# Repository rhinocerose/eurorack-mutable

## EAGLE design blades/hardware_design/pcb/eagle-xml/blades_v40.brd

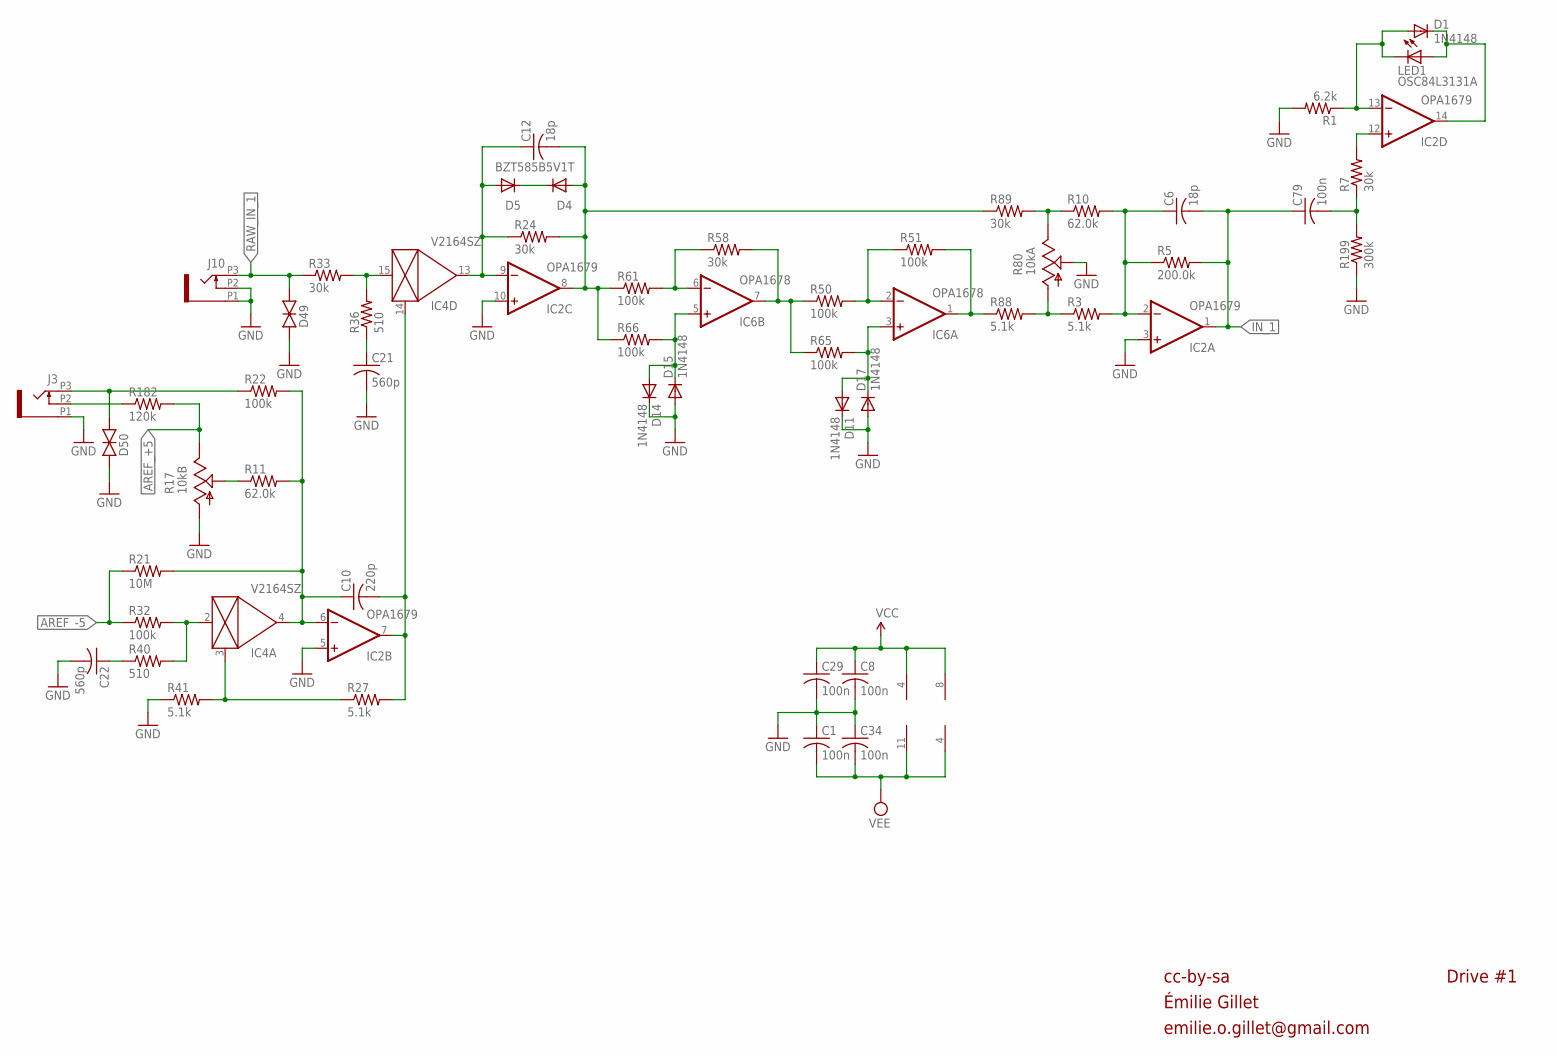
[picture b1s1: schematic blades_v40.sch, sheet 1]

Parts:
C1, C8, C29, C34, C79: 100n; C0402
C6, C12: 18p; C0402
C10: 220p; C0402
C21, C22: 560p; C0402
D1, D11, D14, D15, D17: 1N4148; SOD523
D4, D5: BZT585B5V1T; SOD523
D49, D50: TVS; 0603
IC2: OPA1679; TSSOP14_065
IC4: V2164SZ; SOIC16N
IC6: OPA1678; VSSOP8
J3, J10: PJ301_THONKICONNTME; WQP_PJ_301M_TME
LED1: OSC84L3131A; LED3MM
R1: 6.2k; R0402
R3, R27, R41, R88: 5.1k; R0402
R5: 200.0k; R0402
R7, R24, R33, R58, R89: 30k; R0402
R10, R11: 62.0k; R0402
R17: 10kB; ALPS_POT_VERTICAL_PS
R21: 10M; R0402
R22, R32, R50, R51, R61, R65, R66: 100k; R0402
R36, R40: 510; R0402
R80: 10kA; ALPS_POT_NARROW
R182: 120k; R0402
R199: 300k; R0402

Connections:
AREF_+5: R17.P$1 (E), R182.2; also elsewhere on the board
AREF_-5: R21.1, R32.1; also elsewhere on the board
DRIVE_1: C12.2, D4.A, IC2.8 (OUT), R24.2, R61.1, R66.1, R89.1
GND: C1.1, C8.2, C21.2, C22.2, C29.2, C34.1, D11.C, D14.C, D15.A, D17.A, D49.1 (A), D50.1 (A), IC2.3 (+IN), IC2.5 (+IN), IC2.10 (+IN), J3.P1 (1), J10.P1 (1), J10.P2 (2), R1.2, R17.P$3 (A), R41.1, R80.P$2 (S), R199.1; also elsewhere on the board
IN_1: C6.2, C79.1, IC2.1 (OUT), R5.2; also elsewhere on the board
MORPH_1A1: C10.2, IC2.7 (OUT), IC4.14 (CTRL), R27.2
unnamed: D4.C, D5.C
unnamed: C21.1, R36.1
unnamed: C79.2, R7.1, R199.2
unnamed: IC4.2 (IN), R32.2, R40.2
unnamed: IC2.12 (+IN), R7.2
unnamed: R10.1, R80.P$1 (E), R89.2
unnamed: IC6.6 (-IN), R58.1, R61.2
unnamed: D50.2 (C), J3.P3 (3), R22.1
unnamed: C10.1, IC2.6 (-IN), IC4.4 (OUT), R11.2, R21.2, R22.2
unnamed: R3.1, R80.P$3 (A), R88.2
unnamed: C6.1, IC2.2 (-IN), R3.2, R5.1, R10.2
unnamed: R11.1, R17.P$2 (S)
unnamed: IC4.3 (CTRL), R27.1, R41.2
unnamed: J3.P2 (2), R182.1
unnamed: C22.1, R40.1
unnamed: IC4.15 (IN), R33.2, R36.2
unnamed: D1.A, IC2.13 (-IN), LED1.K (C), R1.1
unnamed: C12.1, D5.A, IC2.9 (-IN), IC4.13 (OUT), R24.1
unnamed: D14.A, D15.C, IC6.5 (+IN), R66.2
unnamed: D1.C, IC2.14 (OUT), LED1.A
unnamed: IC6.7 (OUT), R50.1, R58.2, R65.1
unnamed: IC6.2 (-IN), R50.2, R51.1
unnamed: IC6.1 (OUT), R51.2, R88.1
unnamed: D11.A, D17.C, IC6.3 (+IN), R65.2
RAW_IN_1: D49.2 (C), J10.P3 (3), R33.1; also elsewhere on the board
VCC: C8.1, C29.1, IC2.4 (V+), IC6.8 (V+); also elsewhere on the board
VEE: C1.2, C34.2, IC2.11 (V-), IC6.4 (V-); also elsewhere on the board

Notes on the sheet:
cc-by-sa
Émilie Gillet
emilie.o.gillet@gmail.com
Drive #1

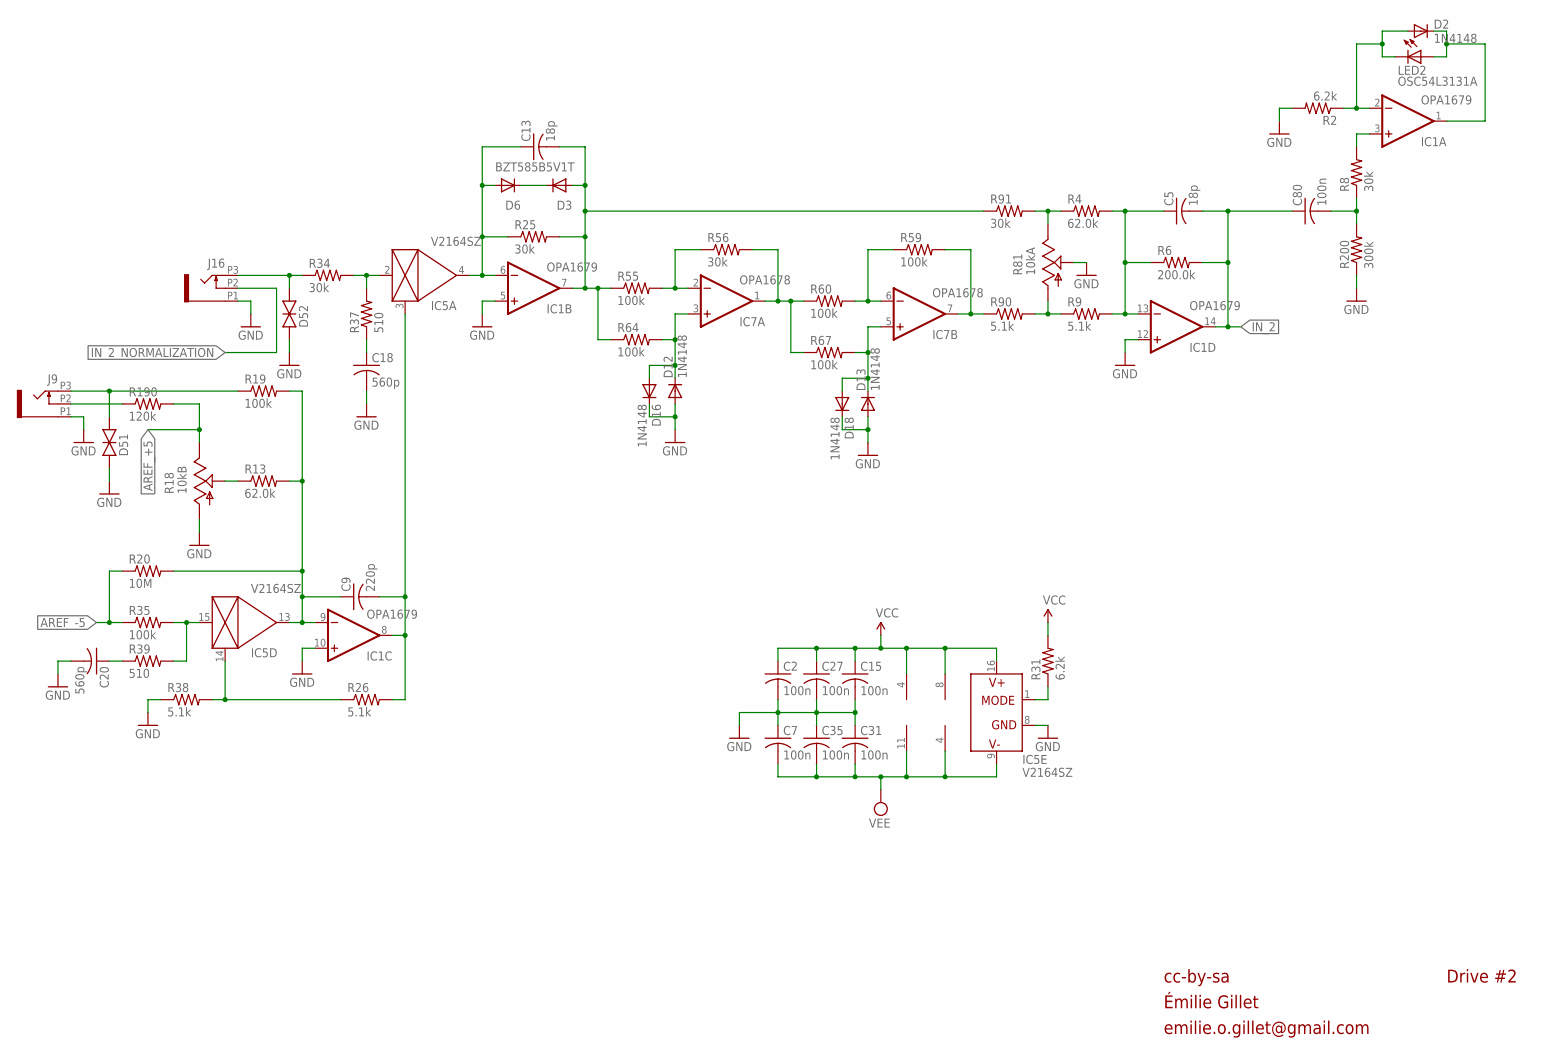
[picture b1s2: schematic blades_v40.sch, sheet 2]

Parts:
C2, C7, C15, C27, C31, C35, C80: 100n; C0402
C5, C13: 18p; C0402
C9: 220p; C0402
C18, C20: 560p; C0402
D2, D12, D13, D16, D18: 1N4148; SOD523
D3, D6: BZT585B5V1T; SOD523
D51, D52: TVS; 0603
IC1: OPA1679; TSSOP14_065
IC5: V2164SZ; SOIC16N
IC7: OPA1678; VSSOP8
J9, J16: PJ301_THONKICONNTME; WQP_PJ_301M_TME
LED2: OSC54L3131A; LED3MM
R2, R31: 6.2k; R0402
R4, R13: 62.0k; R0402
R6: 200.0k; R0402
R8, R25, R34, R56, R91: 30k; R0402
R9, R26, R38, R90: 5.1k; R0402
R18: 10kB; ALPS_POT_VERTICAL_PS
R19, R35, R55, R59, R60, R64, R67: 100k; R0402
R20: 10M; R0402
R37, R39: 510; R0402
R81: 10kA; ALPS_POT_NARROW
R190: 120k; R0402
R200: 300k; R0402

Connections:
AREF_+5: R18.P$1 (E), R190.2; also elsewhere on the board
AREF_-5: R20.1, R35.1; also elsewhere on the board
DRIVE_2: C13.2, D3.A, IC1.7 (OUT), R25.2, R55.1, R64.1, R91.1
GND: C2.2, C7.1, C15.2, C18.2, C20.2, C27.2, C31.1, C35.1, D12.A, D13.A, D16.C, D18.C, D51.1 (A), D52.1 (A), IC1.5 (+IN), IC1.10 (+IN), IC1.12 (+IN), IC5.8 (GND), J9.P1 (1), J16.P1 (1), R2.2, R18.P$3 (A), R38.1, R81.P$2 (S), R200.1; also elsewhere on the board
IN_1LED1: IC1.3 (+IN), R8.2
IN_2: C5.2, C80.1, IC1.14 (OUT), R6.2; also elsewhere on the board
IN_2_NORMALIZATION: J16.P2 (2); also elsewhere on the board
MORPH_1A2: C9.2, IC1.8 (OUT), IC5.3 (CTRL), R26.2
unnamed: D2.A, IC1.2 (-IN), LED2.K (C), R2.1
unnamed: R13.1, R18.P$2 (S)
unnamed: IC7.2 (-IN), R55.2, R56.1
unnamed: D12.C, D16.A, IC7.3 (+IN), R64.2
unnamed: IC7.1 (OUT), R56.2, R60.1, R67.1
unnamed: IC7.6 (-IN), R59.1, R60.2
unnamed: J9.P2 (2), R190.1
unnamed: IC7.7 (OUT), R59.2, R90.1
unnamed: D51.2 (C), J9.P3 (3), R19.1
unnamed: C5.1, IC1.13 (-IN), R4.2, R6.1, R9.2
unnamed: IC5.1 (MODE), R31.1
unnamed: C80.2, R8.1, R200.2
unnamed: D2.C, IC1.1 (OUT), LED2.A
unnamed: C9.1, IC1.9 (-IN), IC5.13 (OUT), R13.2, R19.2, R20.2
unnamed: IC5.14 (CTRL), R26.1, R38.2
unnamed: IC5.15 (IN), R35.2, R39.2
unnamed: C20.1, R39.1
unnamed: C18.1, R37.1
unnamed: IC5.2 (IN), R34.2, R37.2
unnamed: C13.1, D6.A, IC1.6 (-IN), IC5.4 (OUT), R25.1
unnamed: D13.C, D18.A, IC7.5 (+IN), R67.2
unnamed: R4.1, R81.P$1 (E), R91.2
unnamed: R9.1, R81.P$3 (A), R90.2
unnamed: D3.C, D6.C
RAW_IN_2: D52.2 (C), J16.P3 (3), R34.1
VCC: C2.1, C15.1, C27.1, IC1.4 (V+), IC5.16 (V+), IC7.8 (V+), R31.2; also elsewhere on the board
VEE: C7.2, C31.2, C35.2, IC1.11 (V-), IC5.9 (V-), IC7.4 (V-); also elsewhere on the board

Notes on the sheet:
Drive #2
cc-by-sa
Émilie Gillet
emilie.o.gillet@gmail.com

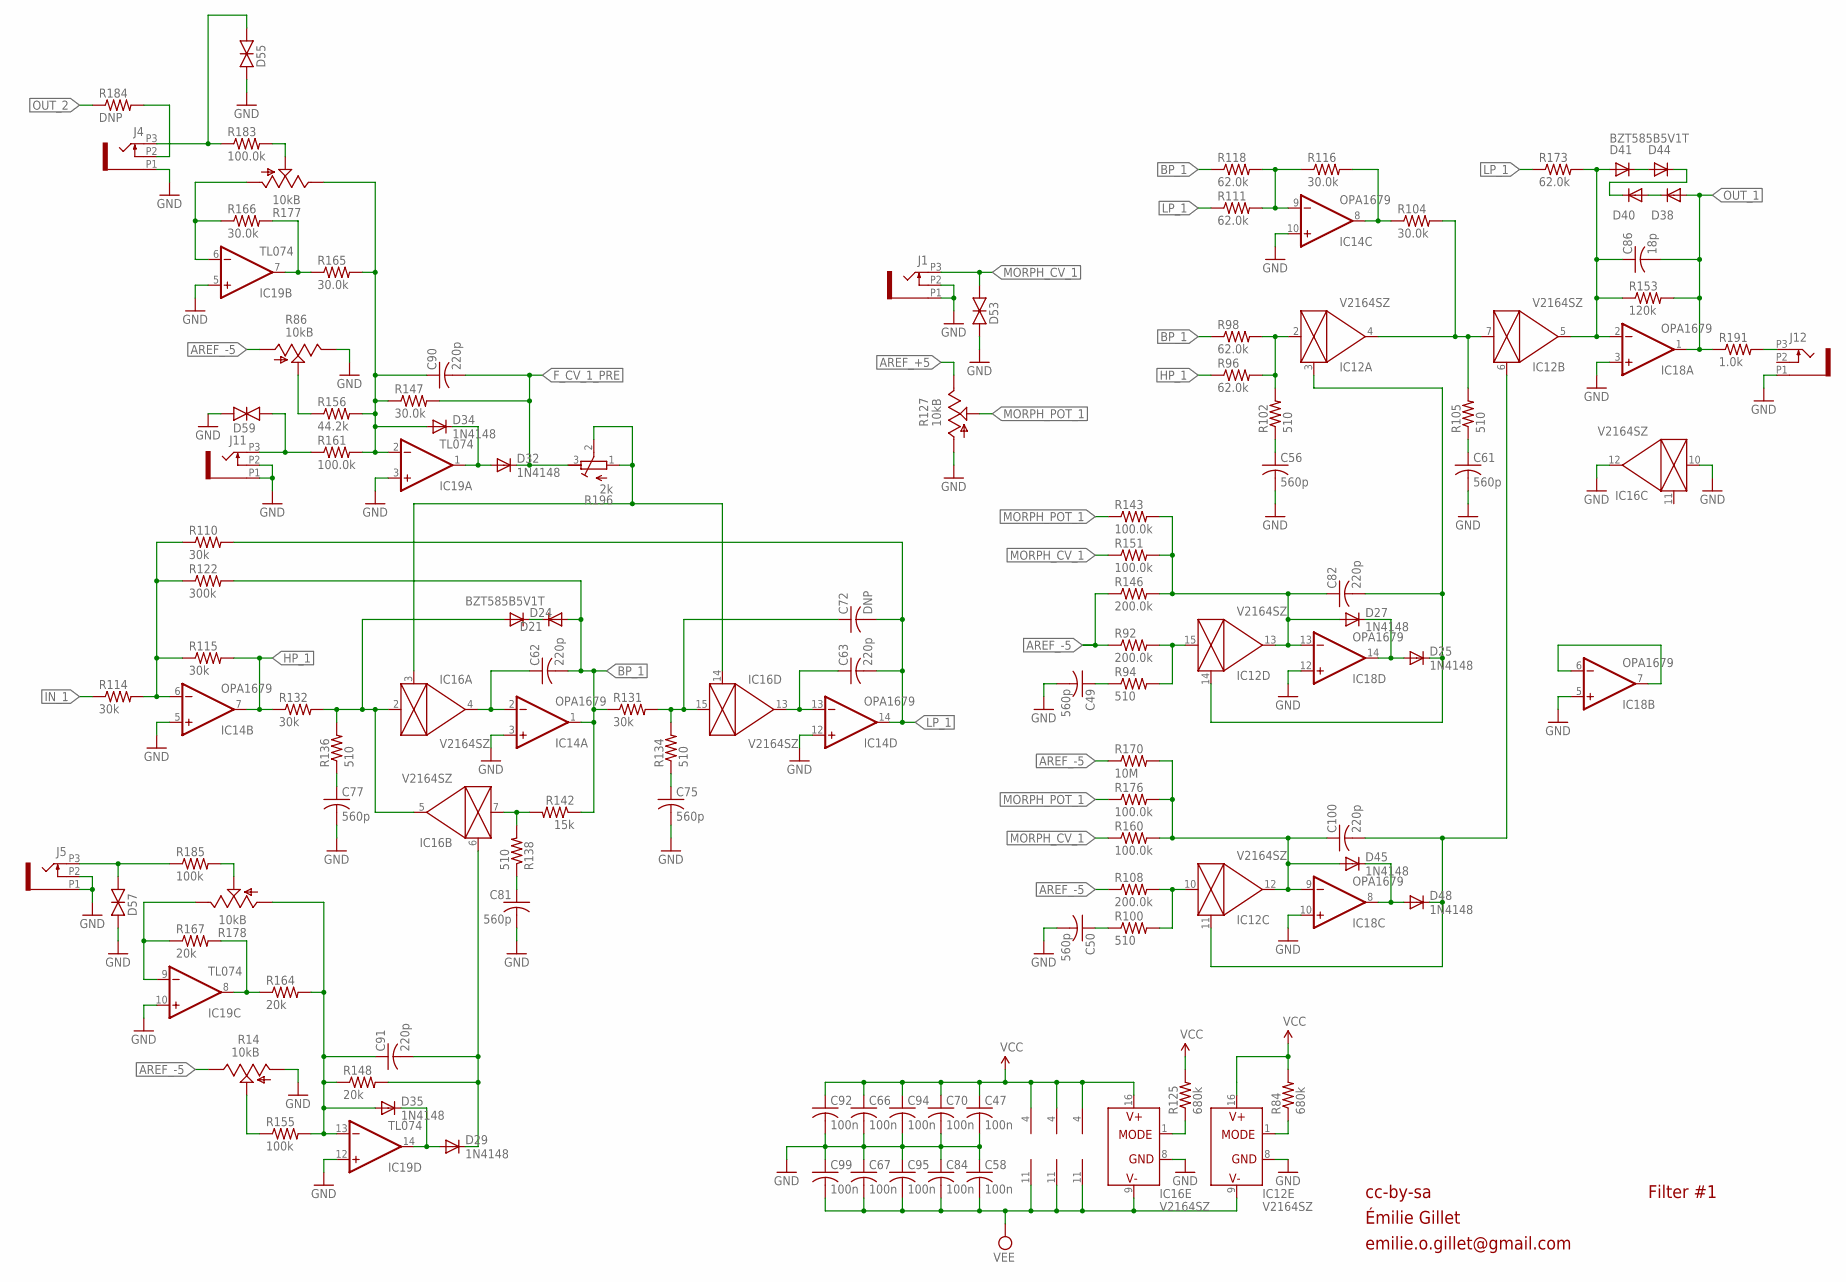
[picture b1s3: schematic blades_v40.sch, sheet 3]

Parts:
C47, C58, C66, C67, C70, C84, C92, C94, C95, C99: 100n; C0402
C49, C50, C56, C61, C75, C77, C81: 560p; C0402
C62, C63, C82, C90, C91, C100: 220p; C0402
C72: DNP; C0402
C86: 18p; C0402
D21, D24, D38, D40, D41, D44: BZT585B5V1T; SOD523
D25, D27, D29, D32, D34, D35, D45, D48: 1N4148; SOD523
D53, D55, D57, D59: TVS; 0603
IC12, IC16: V2164SZ; SOIC16N
IC14, IC18: OPA1679; TSSOP14_065
IC19: TL074; TSSOP14_065
J1, J4, J5, J11, J12: PJ301_THONKICONNTME; WQP_PJ_301M_TME
R14, R86, R127: 10kB; ALPS_POT_VERTICAL_PS
R84, R125: 680k; R0402
R92, R108, R146: 200.0k; R0402
R94, R100, R102, R105, R134, R136, R138: 510; R0402
R96, R98, R111, R118, R173: 62.0k; R0402
R104, R116, R147, R165, R166: 30.0k; R0402
R110, R114, R115, R131, R132: 30k; R0402
R122: 300k; R0402
R142: 15k; R0402
R143, R151, R160, R161, R176, R183: 100.0k; R0402
R148, R164, R167: 20k; R0402
R153: 120k; R0402
R155, R185: 100k; R0402
R156: 44.2k; R0402
R170: 10M; R0402
R177, R178: 10kB; ALPS_POT_NARROW
R184: DNP; R0603
R191: 1.0k; R0603
R196: 2k; RTRIM3296W

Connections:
AREF_+5: R127.P$1 (E); also elsewhere on the board
AREF_-5: R14.P$1 (E), R86.P$3 (A), R92.1, R108.1, R146.1, R170.1; also elsewhere on the board
BP_1: C62.2, D21.A, IC14.1 (OUT), R98.1, R118.1, R122.2, R131.1, R142.1
F_CV_1: IC16.3 (CTRL), IC16.14 (CTRL), R196.1 (E), R196.2 (S)
F_CV_1_PRE: C90.2, D32.C, R147.2, R196.3 (A); also elsewhere on the board
GND: C47.2, C49.2, C50.2, C56.2, C58.1, C61.2, C66.2, C67.1, C70.2, C75.2, C77.2, C81.2, C84.1, C92.2, C94.2, C95.1, C99.1, D53.1 (A), D55.1 (A), D57.1 (A), D59.1 (A), IC12.8 (GND), IC14.3 (+IN), IC14.5 (+IN), IC14.10 (+IN), IC14.12 (+IN), IC16.8 (GND), IC16.10 (IN), IC16.12 (OUT), IC18.3 (+IN), IC18.5 (+IN), IC18.10 (+IN), IC18.12 (+IN), IC19.3 (+IN), IC19.5 (+IN), IC19.10 (+IN), IC19.12 (+IN), J1.P1 (1), J1.P2 (2), J4.P1 (1), J5.P1 (1), J5.P2 (2), J11.P1 (1), J11.P2 (2), J12.P1 (1), R14.P$3 (A), R86.P$1 (E), R127.P$3 (A); also elsewhere on the board
HP_1: IC14.7 (OUT), R96.1, R115.2, R132.1
IN_1: R114.1; also elsewhere on the board
LP_1: C63.2, C72.2, IC14.14 (OUT), R110.2, R111.1, R173.1
MORPH_1A: C82.2, D25.C, IC12.3 (CTRL), IC12.14 (CTRL)
MORPH_1B: C100.2, D48.C, IC12.6 (CTRL), IC12.11 (CTRL)
MORPH_CV_1: D53.2 (C), J1.P3 (3), R151.1, R160.1
MORPH_POT_1: R127.P$2 (S), R143.1, R176.1
unnamed: C77.1, R136.1
unnamed: J12.P3 (3), R191.2
unnamed: C90.1, D34.A, IC19.2 (-IN), R147.1, R156.2, R161.2, R165.2, R177.P$1 (E)
unnamed: C91.1, D35.A, IC19.13 (-IN), R148.1, R155.2, R164.2, R178.P$3 (A)
unnamed: D32.A, D34.C, IC19.1 (OUT)
unnamed: R86.P$2 (S), R156.1
unnamed: IC19.9 (-IN), R167.1, R178.P$1 (E)
unnamed: IC19.8 (OUT), R164.1, R167.2
unnamed: R178.P$2 (S), R185.2
unnamed: C100.1, D45.A, IC12.12 (OUT), IC18.9 (-IN), R160.2, R170.2, R176.2
unnamed: IC14.6 (-IN), R110.1, R114.2, R115.1, R122.1
unnamed: C62.1, IC14.2 (-IN), IC16.4 (OUT)
unnamed: C75.1, R134.1
unnamed: C72.1, IC16.15 (IN), R131.2, R134.2
unnamed: C63.1, IC14.13 (-IN), IC16.13 (OUT)
unnamed: C81.1, R138.1
unnamed: IC16.7 (IN), R138.2, R142.2
unnamed: D57.2 (C), J5.P3 (3), R185.1
unnamed: D29.A, D35.C, IC19.14 (OUT)
unnamed: IC18.6 (-IN), IC18.7 (OUT)
unnamed: J4.P2 (2), R184.2
unnamed: R14.P$2 (S), R155.1
unnamed: IC12.2 (IN), R96.2, R98.2, R102.2
unnamed: IC14.9 (-IN), R111.2, R116.1, R118.2
unnamed: IC14.8 (OUT), R104.1, R116.2
unnamed: IC12.4 (OUT), IC12.7 (IN), R104.2, R105.2
unnamed: C56.1, R102.1
unnamed: C61.1, R105.1
unnamed: D45.C, D48.A, IC18.8 (OUT)
unnamed: IC12.10 (IN), R100.2, R108.2
unnamed: IC19.6 (-IN), R166.1, R177.P$3 (A)
unnamed: IC19.7 (OUT), R165.1, R166.2
unnamed: R177.P$2 (S), R183.2
unnamed: D55.2 (C), J4.P3 (3), R183.1
unnamed: D59.2 (C), J11.P3 (3), R161.1
unnamed: C50.1, R100.1
unnamed: IC12.15 (IN), R92.2, R94.2
unnamed: C49.1, R94.1
unnamed: C82.1, D27.A, IC12.13 (OUT), IC18.13 (-IN), R143.2, R146.2, R151.2
unnamed: D25.A, D27.C, IC18.14 (OUT)
unnamed: IC12.1 (MODE), R84.1
unnamed: IC16.1 (MODE), R125.1
unnamed: D21.C, D24.C
unnamed: C86.1, D41.A, IC12.5 (OUT), IC18.2 (-IN), R153.1, R173.2
unnamed: D38.C, D40.A
unnamed: D24.A, IC16.2 (IN), IC16.5 (OUT), R132.2, R136.2
unnamed: D40.C, D44.C
unnamed: D41.C, D44.A
OUT_1: C86.2, D38.A, IC18.1 (OUT), R153.2, R191.1; also elsewhere on the board
OUT_2: R184.1; also elsewhere on the board
RESONANCE_SUM_1: C91.2, D29.C, IC16.6 (CTRL), R148.2
VCC: C47.1, C66.1, C70.1, C92.1, C94.1, IC12.16 (V+), IC14.4 (V+), IC16.16 (V+), IC18.4 (V+), IC19.4 (V+), R84.2, R125.2; also elsewhere on the board
VEE: C58.2, C67.2, C84.2, C95.2, C99.2, IC12.9 (V-), IC14.11 (V-), IC16.9 (V-), IC18.11 (V-), IC19.11 (V-); also elsewhere on the board

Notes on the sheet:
Filter #1
cc-by-sa
Émilie Gillet
emilie.o.gillet@gmail.com

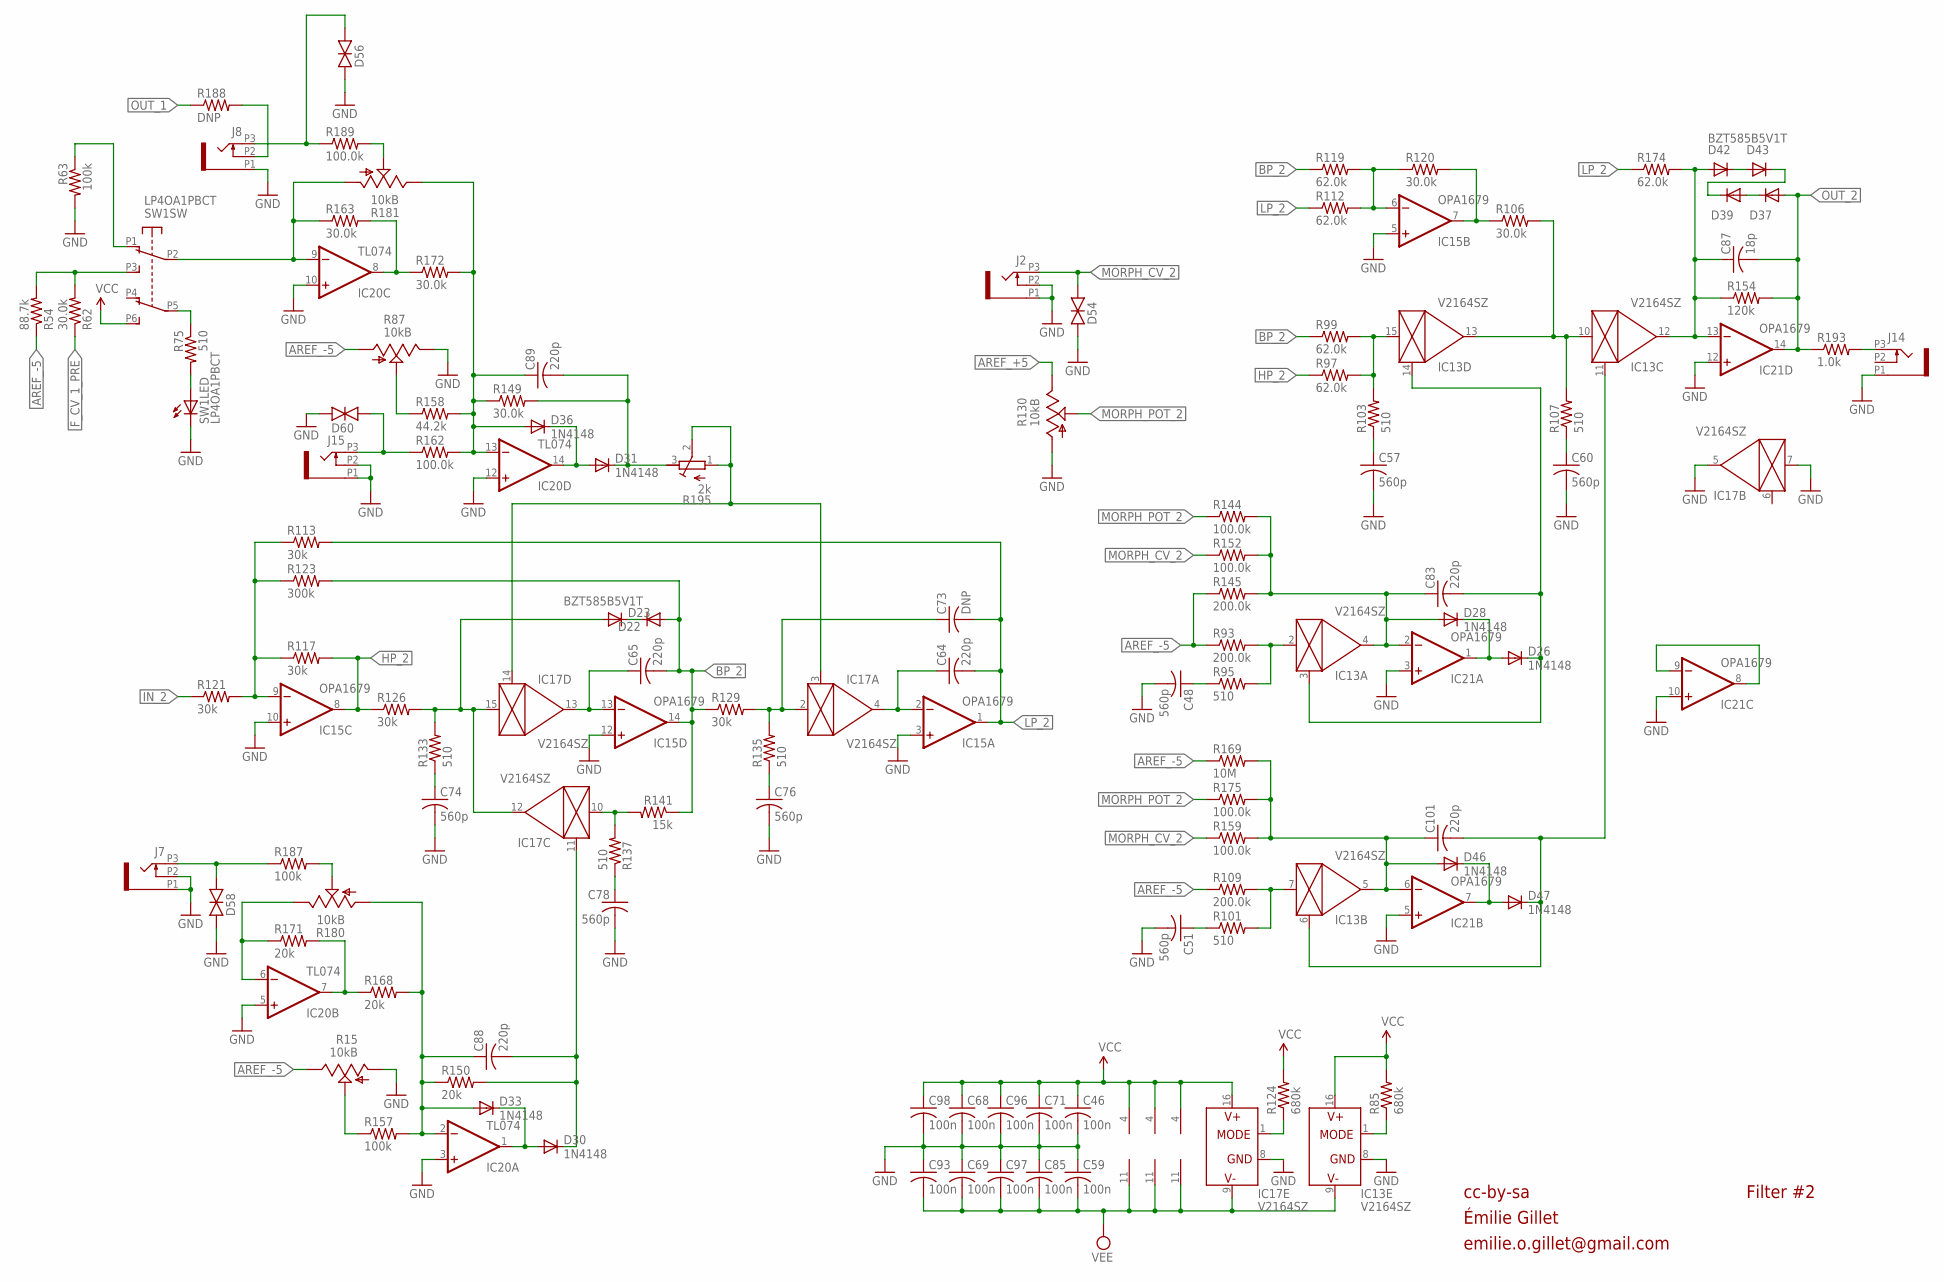
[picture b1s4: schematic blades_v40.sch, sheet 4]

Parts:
C46, C59, C68, C69, C71, C85, C93, C96, C97, C98: 100n; C0402
C48, C51, C57, C60, C74, C76, C78: 560p; C0402
C64, C65, C83, C88, C89, C101: 220p; C0402
C73: DNP; C0402
C87: 18p; C0402
D22, D23, D37, D39, D42, D43: BZT585B5V1T; SOD523
D26, D28, D30, D31, D33, D36, D46, D47: 1N4148; SOD523
D54, D56, D58, D60: TVS; 0603
IC13, IC17: V2164SZ; SOIC16N
IC15, IC21: OPA1679; TSSOP14_065
IC20: TL074; TSSOP14_065
J2, J7, J8, J14, J15: PJ301_THONKICONNTME; WQP_PJ_301M_TME
R15, R87, R130: 10kB; ALPS_POT_VERTICAL_PS
R54: 88.7k; R0402
R62, R106, R120, R149, R163, R172: 30.0k; R0402
R63, R157, R187: 100k; R0402
R75, R95, R101, R103, R107, R133, R135, R137: 510; R0402
R85, R124: 680k; R0402
R93, R109, R145: 200.0k; R0402
R97, R99, R112, R119, R174: 62.0k; R0402
R113, R117, R121, R126, R129: 30k; R0402
R123: 300k; R0402
R141: 15k; R0402
R144, R152, R159, R162, R175, R189: 100.0k; R0402
R150, R168, R171: 20k; R0402
R154: 120k; R0402
R158: 44.2k; R0402
R169: 10M; R0402
R180, R181: 10kB; ALPS_POT_NARROW
R188: DNP; R0603
R193: 1.0k; R0603
R195: 2k; RTRIM3296W
SW1: LP4OA1PBCT

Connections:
AREF_+5: R130.P$1 (E); also elsewhere on the board
AREF_-5: R15.P$1 (E), R54.1, R87.P$3 (A), R93.1, R109.1, R145.1, R169.1; also elsewhere on the board
BP_2: C65.2, D22.A, IC15.14 (OUT), R99.1, R119.1, R123.2, R129.1, R141.1
F_CV_1_PRE: R62.1; also elsewhere on the board
F_CV_2: IC17.3 (CTRL), IC17.14 (CTRL), R195.1 (E), R195.2 (S)
GND: C46.2, C48.2, C51.2, C57.2, C59.1, C60.2, C68.2, C69.1, C71.2, C74.2, C76.2, C78.2, C85.1, C93.1, C96.2, C97.1, C98.2, D54.1 (A), D56.1 (A), D58.1 (A), D60.1 (A), IC13.8 (GND), IC15.3 (+IN), IC15.5 (+IN), IC15.10 (+IN), IC15.12 (+IN), IC17.5 (OUT), IC17.7 (IN), IC17.8 (GND), IC20.3 (+IN), IC20.5 (+IN), IC20.10 (+IN), IC20.12 (+IN), IC21.3 (+IN), IC21.5 (+IN), IC21.10 (+IN), IC21.12 (+IN), J2.P1 (1), J2.P2 (2), J7.P1 (1), J7.P2 (2), J8.P1 (1), J14.P1 (1), J15.P1 (1), J15.P2 (2), R15.P$3 (A), R63.2, R87.P$1 (E), R130.P$3 (A), SW1.L2; also elsewhere on the board
HP_2: IC15.8 (OUT), R97.1, R117.2, R126.1
IN_2: R121.1; also elsewhere on the board
LP_2: C64.2, C73.2, IC15.1 (OUT), R112.1, R113.2, R174.1
MORPH_1A3: C83.2, D26.C, IC13.3 (CTRL), IC13.14 (CTRL)
MORPH_1B1: C101.2, D47.C, IC13.6 (CTRL), IC13.11 (CTRL)
MORPH_CV_2: D54.2 (C), J2.P3 (3), R152.1, R159.1
MORPH_POT_2: R130.P$2 (S), R144.1, R175.1
unnamed: IC21.8 (OUT), IC21.9 (-IN)
unnamed: R75.1, SW1.P5 (B2)
unnamed: D23.A, IC17.12 (OUT), IC17.15 (IN), R126.2, R133.2
unnamed: C89.2, D31.C, R149.2, R195.3 (A)
unnamed: J8.P2 (2), R188.2
unnamed: C87.1, D42.A, IC13.12 (OUT), IC21.13 (-IN), R154.1, R174.2
unnamed: C88.2, D30.C, IC17.11 (CTRL), R150.2
unnamed: D37.C, D39.A
unnamed: R75.2, SW1.L1
unnamed: R63.1, SW1.P1 (A1)
unnamed: C74.1, R133.1
unnamed: IC15.9 (-IN), R113.1, R117.1, R121.2, R123.1
unnamed: C65.1, IC15.13 (-IN), IC17.13 (OUT)
unnamed: C76.1, R135.1
unnamed: C73.1, IC17.2 (IN), R129.2, R135.2
unnamed: C64.1, IC15.2 (-IN), IC17.4 (OUT)
unnamed: C78.1, R137.1
unnamed: IC17.10 (IN), R137.2, R141.2
unnamed: IC13.15 (IN), R97.2, R99.2, R103.2
unnamed: IC15.6 (-IN), R112.2, R119.2, R120.1
unnamed: IC15.7 (OUT), R106.1, R120.2
unnamed: IC13.10 (IN), IC13.13 (OUT), R106.2, R107.2
unnamed: C57.1, R103.1
unnamed: C60.1, R107.1
unnamed: IC20.9 (-IN), R163.1, R181.P$3 (A), SW1.P2 (A2)
unnamed: IC20.8 (OUT), R163.2, R172.1
unnamed: R181.P$2 (S), R189.2
unnamed: D56.2 (C), J8.P3 (3), R189.1
unnamed: D60.2 (C), J15.P3 (3), R162.1
unnamed: D30.A, D33.C, IC20.1 (OUT)
unnamed: J14.P3 (3), R193.2
unnamed: R87.P$2 (S), R158.1
unnamed: IC20.6 (-IN), R171.1, R180.P$1 (E)
unnamed: IC20.7 (OUT), R168.1, R171.2
unnamed: R180.P$2 (S), R187.2
unnamed: D58.2 (C), J7.P3 (3), R187.1
unnamed: R15.P$2 (S), R157.1
unnamed: R54.2, R62.2, SW1.P3 (A3)
unnamed: C88.1, D33.A, IC20.2 (-IN), R150.1, R157.2, R168.2, R180.P$3 (A)
unnamed: C89.1, D36.A, IC20.13 (-IN), R149.1, R158.2, R162.2, R172.2, R181.P$1 (E)
unnamed: C83.1, D28.A, IC13.4 (OUT), IC21.2 (-IN), R144.2, R145.2, R152.2
unnamed: D26.A, D28.C, IC21.1 (OUT)
unnamed: C101.1, D46.A, IC13.5 (OUT), IC21.6 (-IN), R159.2, R169.2, R175.2
unnamed: D46.C, D47.A, IC21.7 (OUT)
unnamed: D31.A, D36.C, IC20.14 (OUT)
unnamed: IC13.7 (IN), R101.2, R109.2
unnamed: C51.1, R101.1
unnamed: IC13.2 (IN), R93.2, R95.2
unnamed: C48.1, R95.1
unnamed: IC13.1 (MODE), R85.1
unnamed: IC17.1 (MODE), R124.1
unnamed: D22.C, D23.C
unnamed: D42.C, D43.A
unnamed: D39.C, D43.C
OUT_1: R188.1; also elsewhere on the board
OUT_2: C87.2, D37.A, IC21.14 (OUT), R154.2, R193.1; also elsewhere on the board
VCC: C46.1, C68.1, C71.1, C96.1, C98.1, IC13.16 (V+), IC15.4 (V+), IC17.16 (V+), IC20.4 (V+), IC21.4 (V+), R85.2, R124.2, SW1.P6 (B3); also elsewhere on the board
VEE: C59.2, C69.2, C85.2, C93.2, C97.2, IC13.9 (V-), IC15.11 (V-), IC17.9 (V-), IC20.11 (V-), IC21.11 (V-); also elsewhere on the board

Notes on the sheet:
Filter #2
cc-by-sa
Émilie Gillet
emilie.o.gillet@gmail.com

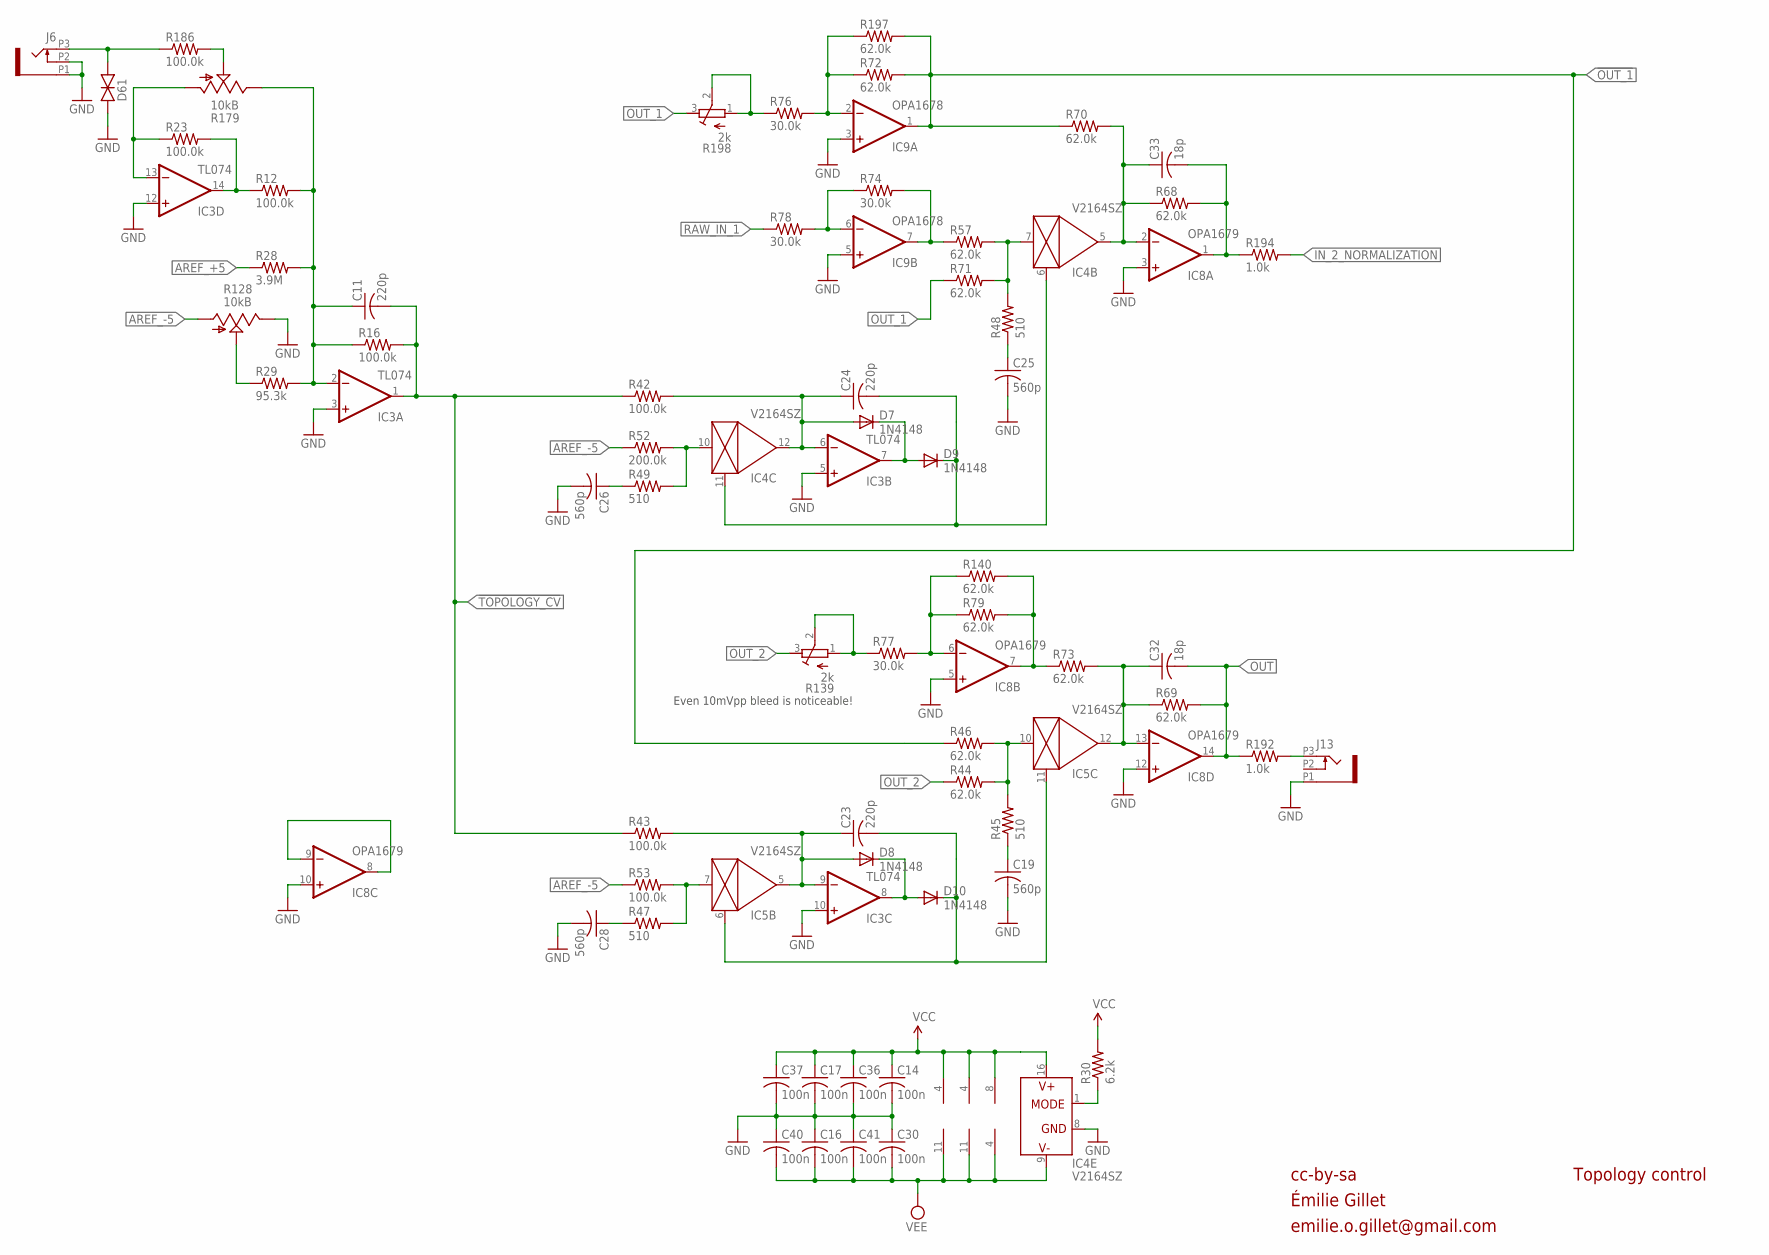
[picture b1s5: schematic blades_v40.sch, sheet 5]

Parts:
C11, C23, C24: 220p; C0402
C14, C16, C17, C30, C36, C37, C40, C41: 100n; C0402
C19, C25, C26, C28: 560p; C0402
C32, C33: 18p; C0402
D7, D8, D9, D10: 1N4148; SOD523
D61: TVS; 0603
IC3: TL074; TSSOP14_065
IC4, IC5: V2164SZ; SOIC16N
IC8: OPA1679; TSSOP14_065
IC9: OPA1678; VSSOP8
J6, J13: PJ301_THONKICONNTME; WQP_PJ_301M_TME
R12, R16, R23, R42, R43, R53, R186: 100.0k; R0402
R28: 3.9M; R0402
R29: 95.3k; R0402
R30: 6.2k; R0402
R44, R46, R57, R68, R69, R70, R71, R72, R73, R79, R140, R197: 62.0k; R0402
R45, R47, R48, R49: 510; R0402
R52: 200.0k; R0402
R74, R76, R77, R78: 30.0k; R0402
R128: 10kB; ALPS_POT_VERTICAL_PS
R139, R198: 2k; RTRIM3296W
R179: 10kB; ALPS_POT_NARROW
R192, R194: 1.0k; R0603

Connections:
!OUT_1: IC9.1 (OUT), R46.1, R70.1, R72.2, R197.2
!TOPOLOGY_CV: C11.2, IC3.1 (OUT), R16.2, R42.1, R43.1
AREF_+5: R28.1; also elsewhere on the board
AREF_-5: R52.1, R53.1, R128.P$3 (A); also elsewhere on the board
F1: C24.2, D9.C, IC4.6 (CTRL), IC4.11 (CTRL)
F2: C23.2, D10.C, IC5.6 (CTRL), IC5.11 (CTRL)
F_CV_3: R77.1, R139.1 (E), R139.2 (S)
GND: C14.2, C16.1, C17.2, C19.2, C25.2, C26.2, C28.2, C30.1, C36.2, C37.2, C40.1, C41.1, D61.1 (A), IC3.3 (+IN), IC3.5 (+IN), IC3.10 (+IN), IC3.12 (+IN), IC4.8 (GND), IC8.3 (+IN), IC8.5 (+IN), IC8.10 (+IN), IC8.12 (+IN), IC9.3 (+IN), IC9.5 (+IN), J6.P1 (1), J6.P2 (2), J13.P1 (1), R128.P$1 (E); also elsewhere on the board
IN_2_NORMALIZATION: R194.2; also elsewhere on the board
unnamed: IC9.6 (-IN), R74.1, R78.2
unnamed: IC5.10 (IN), R44.2, R45.2, R46.2
unnamed: IC8.6 (-IN), R77.2, R79.1, R140.1
unnamed: IC8.7 (OUT), R73.1, R79.2, R140.2
unnamed: IC9.7 (OUT), R57.1, R74.2
unnamed: IC4.7 (IN), R48.2, R57.2, R71.2
unnamed: C32.1, IC5.12 (OUT), IC8.13 (-IN), R69.1, R73.2
unnamed: C19.1, R45.1
unnamed: IC9.2 (-IN), R72.1, R76.2, R197.1
unnamed: C25.1, R48.1
unnamed: C33.1, IC4.5 (OUT), IC8.2 (-IN), R68.1, R70.2
unnamed: C23.1, D8.A, IC3.9 (-IN), IC5.5 (OUT), R43.2
unnamed: IC4.10 (IN), R49.2, R52.2
unnamed: J13.P3 (3), R192.2
unnamed: D8.C, D10.A, IC3.8 (OUT)
unnamed: C26.1, R49.1
unnamed: IC8.8 (OUT), IC8.9 (-IN)
unnamed: C11.1, IC3.2 (-IN), R12.2, R16.1, R28.2, R29.2, R179.P$1 (E)
unnamed: D61.2 (C), J6.P3 (3), R186.1
unnamed: R29.1, R128.P$2 (S)
unnamed: C24.1, D7.A, IC3.6 (-IN), IC4.12 (OUT), R42.2
unnamed: D7.C, D9.A, IC3.7 (OUT)
unnamed: IC5.7 (IN), R47.2, R53.2
unnamed: C28.1, R47.1
unnamed: R179.P$2 (S), R186.2
unnamed: IC3.14 (OUT), R12.1, R23.2
unnamed: IC3.13 (-IN), R23.1, R179.P$3 (A)
unnamed: R76.1, R198.1 (E), R198.2 (S)
unnamed: IC4.1 (MODE), R30.1
OUT: C32.2, IC8.14 (OUT), R69.2, R192.1
OUT_1: R71.1, R198.3 (A); also elsewhere on the board
OUT_2: R44.1, R139.3 (A); also elsewhere on the board
RAW_IN_1: R78.1; also elsewhere on the board
VCC: C14.1, C17.1, C36.1, C37.1, IC3.4 (V+), IC4.16 (V+), IC8.4 (V+), IC9.8 (V+), R30.2; also elsewhere on the board
VEE: C16.2, C30.2, C40.2, C41.2, IC3.11 (V-), IC4.9 (V-), IC8.11 (V-), IC9.4 (V-); also elsewhere on the board
ZZZZ: C33.2, IC8.1 (OUT), R68.2, R194.1

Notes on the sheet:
Topology control
Even 10mVpp bleed is noticeable!
cc-by-sa
Émilie Gillet
emilie.o.gillet@gmail.com

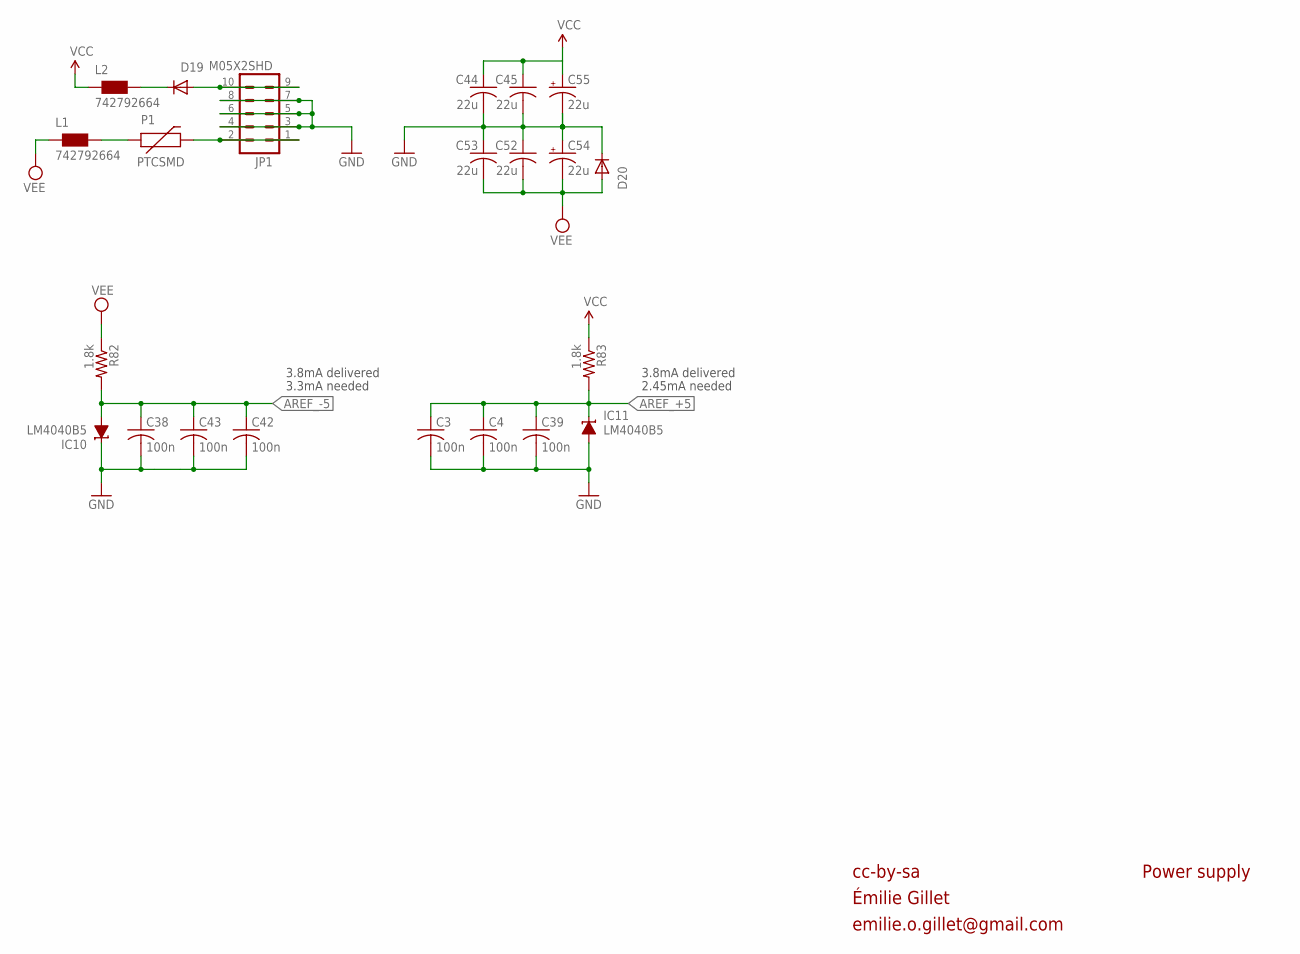
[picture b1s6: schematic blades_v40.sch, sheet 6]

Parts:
C3, C4, C38, C39, C42, C43: 100n; C0402
C44, C45, C52, C53: 22u; C1206
C54, C55: 22u; PANASONIC_B
D19, D20: 1N5819HW; SOD123
IC10, IC11: LM4040B5; DBZ_R-PDSO-G3
JP1: M05X2SHD; 2X5-SHROUDED
L1, L2: 742792664; 0603
P1: PTCSMD; PTC-1206
R82, R83: 1.8k; R0402

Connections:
AREF_+5: C3.1, C4.1, C39.1, IC11.1 (C), R83.2; also elsewhere on the board
AREF_-5: C38.1, C42.1, C43.1, IC10.2 (A), R82.2; also elsewhere on the board
GND: C3.2, C4.2, C38.2, C39.2, C42.2, C43.2, C44.2, C45.2, C52.1, C53.1, C54.+, C55.-, D20.C, IC10.1 (C), IC11.2 (A), JP1.3, JP1.4, JP1.5, JP1.6, JP1.7, JP1.8; also elsewhere on the board
unnamed: JP1.1, JP1.2, P1.2
unnamed: D19.A, JP1.9, JP1.10
unnamed: L1.2, P1.1
unnamed: D19.C, L2.2
VCC: C44.1, C45.1, C55.+, L2.1, R83.1; also elsewhere on the board
VEE: C52.2, C53.2, C54.-, D20.A, L1.1, R82.1; also elsewhere on the board

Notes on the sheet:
Power supply
3.3mA needed
2.45mA needed
3.8mA delivered
cc-by-sa
Émilie Gillet
emilie.o.gillet@gmail.com

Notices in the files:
blades/hardware_design/pcb/eagle-xml/blades_v40.brd:
cc-by-sa É. Gillet
kinks/hardware_design/pcb/eagle-xml/kinks_v41.brd:
cc-by-sa Émilie Gillet, 2015. v4
